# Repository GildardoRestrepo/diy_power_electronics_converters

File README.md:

# Portable Power Electronics Converters

Portable, enclosed power converters for teaching, sized to the supplies and loads of the Electric Machines Laboratory at Universidad Pontificia Bolivariana (UPB). Every unit follows the same path: calculation, simulation, PCB, build and lab validation. Each design can be reviewed and reproduced end to end.

> [!WARNING]
> These converters operate at up to 300 V DC and at mains-level AC. Build and test them only under lab supervision, with proper isolation and protection.

---

## Converters

| Family |             Converter             |     |
| :----: | :-------------------------------: | :-: |
| AC/DC  |  Three-phase full-wave rectifier  |     |
| DC/DC  |          Buck Converter           |     |
| DC/DC  |          Boost Converter          |     |
| DC/AC  | Three-phase full-wave (One level) |     |

### Rectifier
|              Parameter              |               Value               |                         Note                         |     |
| :---------------------------------: | :-------------------------------: | :--------------------------------------------------: | --- |
| Line voltage at the bridge (𝑉𝐿𝐿) |             208 Vrms              | Lab mains or transformer secondary of the same ratio |     |
|         Line frequency (𝑓)         |               60 Hz               |                       Colombia                       |     |
|       Rated DC current (𝐼𝑑)       |                5 A                |        Continuous, lamp bank or reactor load         |     |
|         Maximum DC current          |                8 A                |     10 min, heatsink-limited (see losses report)     |     |
|                Load                 | Resistive (lamps) or RL (reactor) |     𝐿𝑙𝑜𝑎𝑑 large enough for continuous 𝑖𝑑      |     |
|            Pulse number             |                 6                 |       Single box; 12 or 24 with several boxes        |     |

### Buck
|           Parameter            |                     Value                     |                    Note                    |
| :----------------------------: | :-------------------------------------------: | :----------------------------------------: |
|     Input voltage (𝑉𝑖𝑛)     |           280 V nominal, 150–320 V            | Rectifier output at 208 VLL; "300 V" class |
|     Output voltage (𝑉𝑜)      |                     110 V                     |              110 V lamp bank               |
|   Rated output power (𝑃𝑜)    |                     200 W                     |        Two 100 W lamps in parallel         |
|     Output current (𝐼𝑜)      |                    1.82 A                     |           𝑅 =𝑉2𝑜/𝑃𝑜 =60.5 Ω           |
|  Switching frequency (𝑓𝑠𝑤)  |        20 kHz nominal, 5–50 kHz usable        |   IGBT up to 20 kHz, MOSFET up to 50 kHz   |
| Inductor current ripple target |           ≤40 % of 𝐼𝑜 at nominal            |     Shared inductor with the boost box     |
|  Output voltage ripple target  |                     ≤1 %                      |                                            |
|            Control             | Open loop, duty cycle set on the gating block |        No feedback in this version         |

### Boost

|Parameter|Value|Note|
|:-:|:-:|:-:|
|Input voltage (𝑉𝑖𝑛)|110 V nominal, 60–120 V|Lab DC supply (110 V max.)|
|Output voltage (𝑉𝑜)|300 V|Feeds the buck or the inverter box, or a series lamp bank|
|Rated output power (𝑃𝑜)|200 W||
|Output current (𝐼𝑜)|0.667 A|𝑅 =𝑉2𝑜/𝑃𝑜 =450 Ω|
|Switching frequency (𝑓𝑠𝑤)|20 kHz nominal, 5–50 kHz usable|IGBT up to 20 kHz, MOSFET up to 50 kHz|
|Inductor current ripple target|≤40 % of 𝐼𝐿 at nominal|Same 4.7 mH inductor as the buck box|
|Output voltage ripple target|≤1 %||
|Control|Open loop, duty cycle set on the gating block|Over-voltage trip mandatory (see section 6)|

### Inverter

|          Parameter           |                             Value                              |                 Note                 |
| :--------------------------: | :------------------------------------------------------------: | :----------------------------------: |
|   DC-link voltage (𝑉𝑑𝑐)   |                    280 V nominal, 60–320 V                     |                                      |
|  Rated output power (𝑃𝑜)   |                             300 W                              |    Lamp bank (Y or Δ) or reactor     |
|     Rated phase current      |                             2 Arms                             |          𝐼𝑚 =2.83 A peak           |
|    Output frequency (𝑓1)    |                   0.1–400 Hz, 60 Hz default                    |                                      |
| Switching frequency (𝑓𝑠𝑤) |              10 kHz nominal (IGBT), up to 20 kHz               |                                      |
|          Modulation          | Sinusoidal PWM (𝑚𝑎 ≤1), six-step (180∘) and 120∘ square wave |     Selected on the gating block     |
|          Dead time           |                         1.5 𝜇s (IGBT)                         |    Generated by the gating block     |
|        Output filter         |              None on board (optional external LC)              | Lamps and reactor accept PWM voltage |

## Repository structure

The repository is organized by converter family. Every family uses the same five stages, and each stage is numbered after its family (e.g. `2x` for DC/DC).

```
├── 00_docs/
	├── datasheets/
	├── formulas/
	├── architecture.md
	├── gate_bus_interface.md
├── 01_rectifier/
	├── 00_assets/
	├── 10_math/
		├── 11_ideal.md
		├── 12_losses.md
	├── 20_psim/
		├── 20_ideal.psim
		├── 21_losses.psim
	├── 30_pcb/
		├── rectifier_6p/
		├── scripts/
			├── gen_rectifier.py
			├── pcb_config.JSON
	├── 40_building/
	├── 60_tests/
├── 02_buck/
	├── ...                      (same logic as 01)
├── 03_boost/
	├── ...                      (same logic as 01)
├── 04_inverter/
	├── ...                      (same logic as 01) 
├── 05_gating_block
	├── 10_math/
		├── signal_budget.md
	├── 30_pcb/
		├── gating_block/
		├── scripts/
			├── gen_gating_block.py
			├── pcb_config.JSON
├── 90_tools
├── LICENSE
└── README.md
```

---

## Workflow
1. **Math**: requirements, operating point and component sizing.
2. **Simulation**: validation in PSIM, first with ideal and then with real device models.
3. **Electronics design**: schematic and layout in KiCad.
4. **3d**: Case design in Fusion 360.
5. **Building**: Assembly and details.
6. **Tests:** lab tetsting and results.

---

## Tools & Software

|      Purpose      |                 Tool                  |
| :---------------: | :-----------------------------------: |
|    Simulation     |                 PSIM                  |
| Schematic and PCB |                 KiCad                 |
| Enclosure design  |              Fusion 360               |
| Switching control |          ESP32 + Arduino IDE          |
|     Lab tests     | Electrical Machines Laboratory at UPB |

---

## License

Released under the [MIT License](LICENSE).

---

## Enlaces

[[power_electronics|Power Electronics]]

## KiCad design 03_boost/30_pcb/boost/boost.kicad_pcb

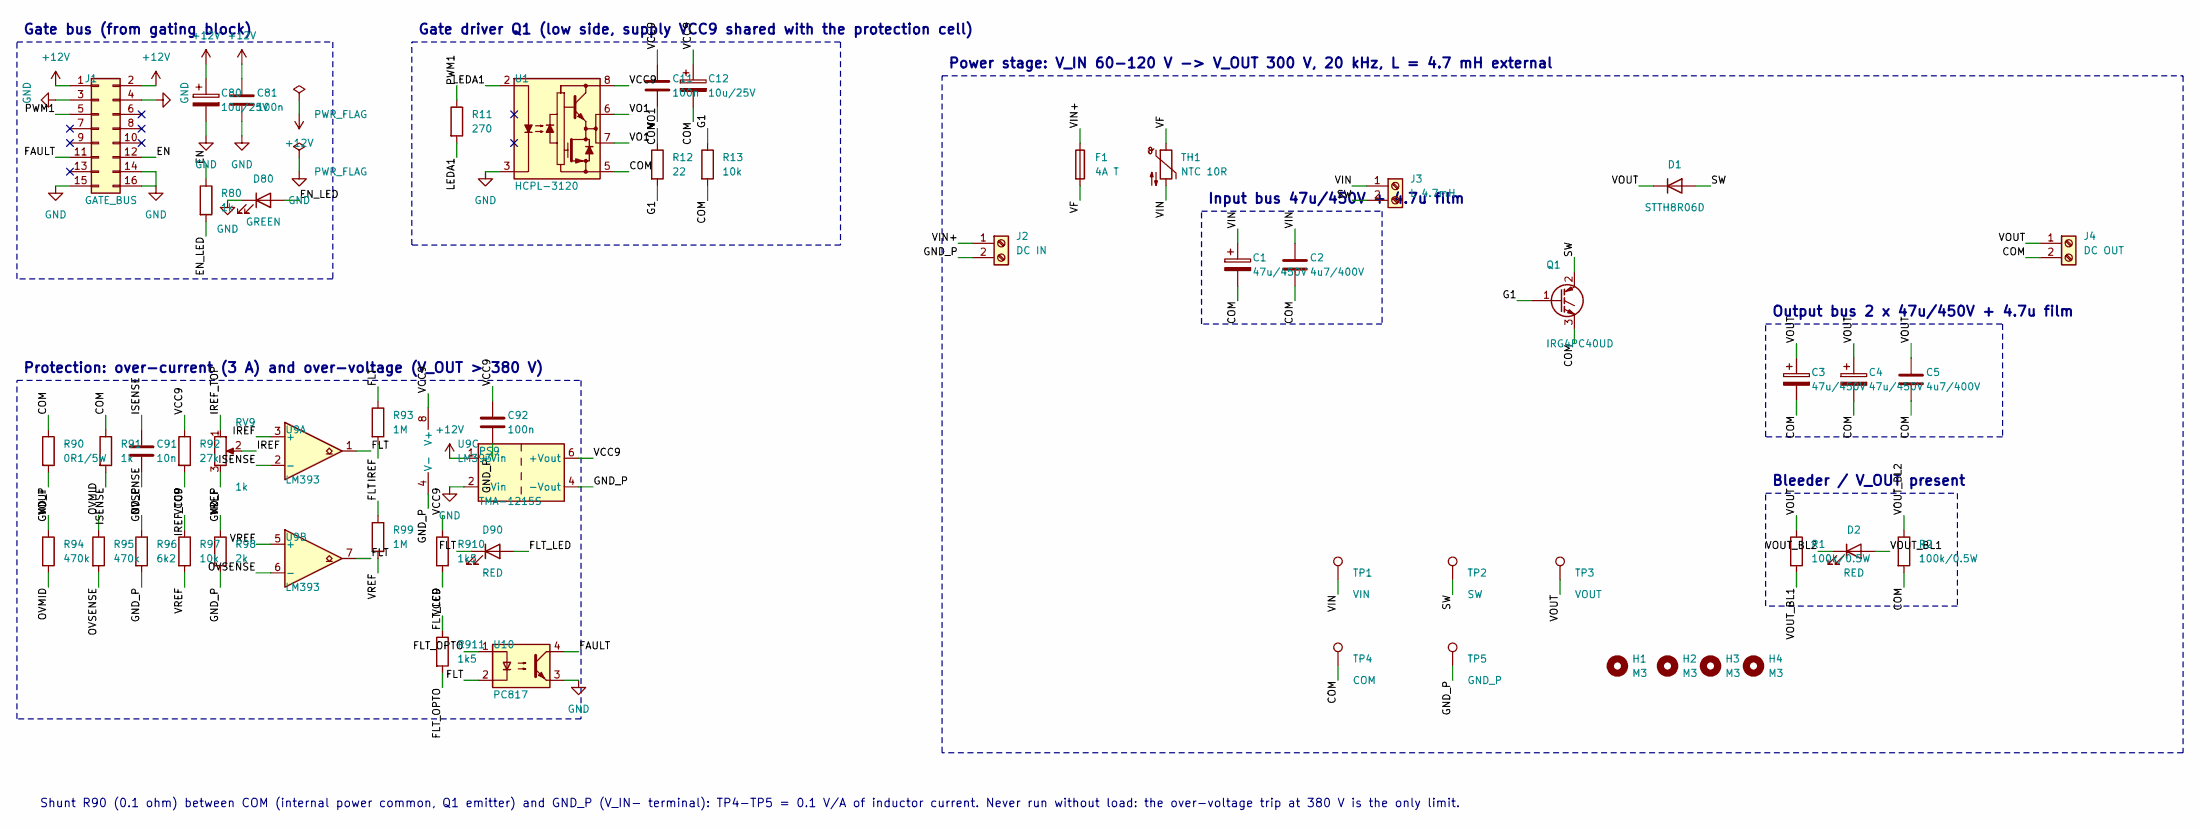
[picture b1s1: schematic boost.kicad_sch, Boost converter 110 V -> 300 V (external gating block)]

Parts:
C1, C3, C4: 47u/450V; C_Radial_D16.0mm_H25.0mm_P7.50mm
C2, C5: 4u7/400V; C_Rect_L31.5mm_W15.0mm_P27.50mm_MKS4
C11, C81, C92: 100n; C_Disc_D5.0mm_W2.5mm_P5.00mm
C12, C80: 10u/25V; C_Radial_D6.3mm_H11.0mm_P2.50mm
C91: 10n; C_Disc_D5.0mm_W2.5mm_P5.00mm
D1: STTH8R06D; TO-220-2_Vertical
D2: RED; LED_D5.0mm
D80: GREEN; LED_D3.0mm
D90: RED; LED_D3.0mm
F1: 4A T; Fuseholder_Cylinder-5x20mm_Schurter_0031_8201_Horizontal_Op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
H1, H2, H3, H4: M3; MountingHole_3.2mm_M3
J1: GATE_BUS; IDC-Header_2x08-1MP_P2.54mm_Latch9.5mm_Vertical
J2: DC IN; TerminalBlock_Phoenix_MKDS-1,5-2-5.08_1x02_P5.08mm_Horizont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
J3: L 4.7mH; TerminalBlock_Phoenix_MKDS-1,5-2-5.08_1x02_P5.08mm_Horizont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
J4: DC OUT; TerminalBlock_Phoenix_MKDS-1,5-2-5.08_1x02_P5.08mm_Horizont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
PS9: TMA-1215S; Converter_DCDC_TRACO_TMA-05xxS_12xxS_Single_THT
Q1: IRG4PC40UD; TO-247-3_Vertical
R1, R2: 100k/0.5W; R_Axial_DIN0414_L11.9mm_D4.5mm_P15.24mm_Horizontal
R11: 270; R_Axial_DIN0207_L6.3mm_D2.5mm_P10.16mm_Horizontal
R12: 22; R_Axial_DIN0207_L6.3mm_D2.5mm_P10.16mm_Horizontal
R13, R97: 10k; R_Axial_DIN0207_L6.3mm_D2.5mm_P10.16mm_Horizontal
R80, R91: 1k; R_Axial_DIN0207_L6.3mm_D2.5mm_P10.16mm_Horizontal
R90: 0R1/5W; R_Axial_Power_L20.0mm_W6.4mm_P25.40mm
R92: 27k; R_Axial_DIN0207_L6.3mm_D2.5mm_P10.16mm_Horizontal
R93, R99: 1M; R_Axial_DIN0207_L6.3mm_D2.5mm_P10.16mm_Horizontal
R94, R95: 470k; R_Axial_DIN0414_L11.9mm_D4.5mm_P15.24mm_Horizontal
R96: 6k2; R_Axial_DIN0207_L6.3mm_D2.5mm_P10.16mm_Horizontal
R98: 2k; R_Axial_DIN0207_L6.3mm_D2.5mm_P10.16mm_Horizontal
R910, R911: 1k5; R_Axial_DIN0207_L6.3mm_D2.5mm_P10.16mm_Horizontal
RV9: 1k; Potentiometer_Bourns_3296W_Vertical
TH1: NTC 10R; RV_Disc_D15.5mm_W4.2mm_P7.5mm
TP1: VIN; TestPoint_Loop_D2.50mm_Drill1.0mm
TP2: SW; TestPoint_Loop_D2.50mm_Drill1.0mm
TP3: VOUT; TestPoint_Loop_D2.50mm_Drill1.0mm
TP4: COM; TestPoint_Loop_D2.50mm_Drill1.0mm
TP5: GND_P; TestPoint_Loop_D2.50mm_Drill1.0mm
U1: HCPL-3120; DIP-8_W7.62mm
U9: LM393; DIP-8_W7.62mm
U10: PC817; DIP-4_W7.62mm

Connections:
+12V: C80.1, C81.1, J1.1, J1.2, PS9.1 (+Vin)
/COM: C1.2, C2.2, C3.2, C4.2, C5.2, C11.2, C12.2, J4.2, Q1.3 (E), R2.2, R13.2, R90.1, R91.1, TP4.1, U1.5 (VEE)
/EN: J1.12, R80.1
/EN_LED: D80.2 (A), R80.2
/FAULT: J1.11, U10.4
/FLT: D90.1 (K), R93.1, R99.1, U9.1, U9.7, U10.2
/FLT_LED: D90.2 (A), R910.2
/FLT_OPTO: R911.2, U10.1
/G1: Q1.1 (G), R12.2, R13.1
/GND_P: C91.2, C92.2, J2.2, PS9.4 (-Vout), R90.2, R96.2, R98.2, RV9.3, TP5.1, U9.4 (V-)
/IREF: R93.2, RV9.2, U9.3 (+)
/IREF_TOP: R92.2, RV9.1
/ISENSE: C91.1, R91.2, U9.2 (-)
/LEDA1: R11.2, U1.2 (A)
/OVMID: R94.2, R95.1
/OVSENSE: R95.2, R96.1, U9.6 (-)
/PWM1: J1.5, R11.1
/SW: D1.2 (A), J3.2, Q1.2 (C), TP2.1
/VCC9: C11.1, C12.1, C92.1, PS9.6 (+Vout), R92.1, R97.1, R910.1, R911.1, U1.8 (VCC), U9.8 (V+)
/VF: F1.2, TH1.1
/VIN: C1.1, C2.1, J3.1, TH1.2, TP1.1
/VIN+: F1.1, J2.1
/VO1: R12.1, U1.6 (VO), U1.7 (VO)
/VOUT: C3.1, C4.1, C5.1, D1.1 (K), J4.1, R1.1, R94.1, TP3.1
/VOUT_BL1: D2.2 (A), R1.2
/VOUT_BL2: D2.1 (K), R2.1
/VREF: R97.2, R98.1, R99.2, U9.5 (+)
GND: C80.2, C81.2, D80.1 (K), J1.3, J1.4, J1.14, J1.15, J1.16, PS9.2 (-Vin), U1.3 (C), U10.3

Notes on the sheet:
Gate bus (from gating block)
Gate driver Q1 (low side, supply VCC9 shared with the protection cell)
Protection: over-current (3 A) and over-voltage (V_OUT > 380 V)
Power stage: V_IN 60-120 V -> V_OUT 300 V, 20 kHz, L = 4.7 mH external
Input bus 47u/450V + 4.7u film
Output bus 2 x 47u/450V + 4.7u film
Bleeder / V_OUT present
Shunt R90 (0.1 ohm) between COM (internal power common, Q1 emitter) and GND_P (V_IN- terminal): TP4-TP5 = 0.1 V/A of inductor current. Never run without load: the over-voltage trip at 380 V is the only limit.

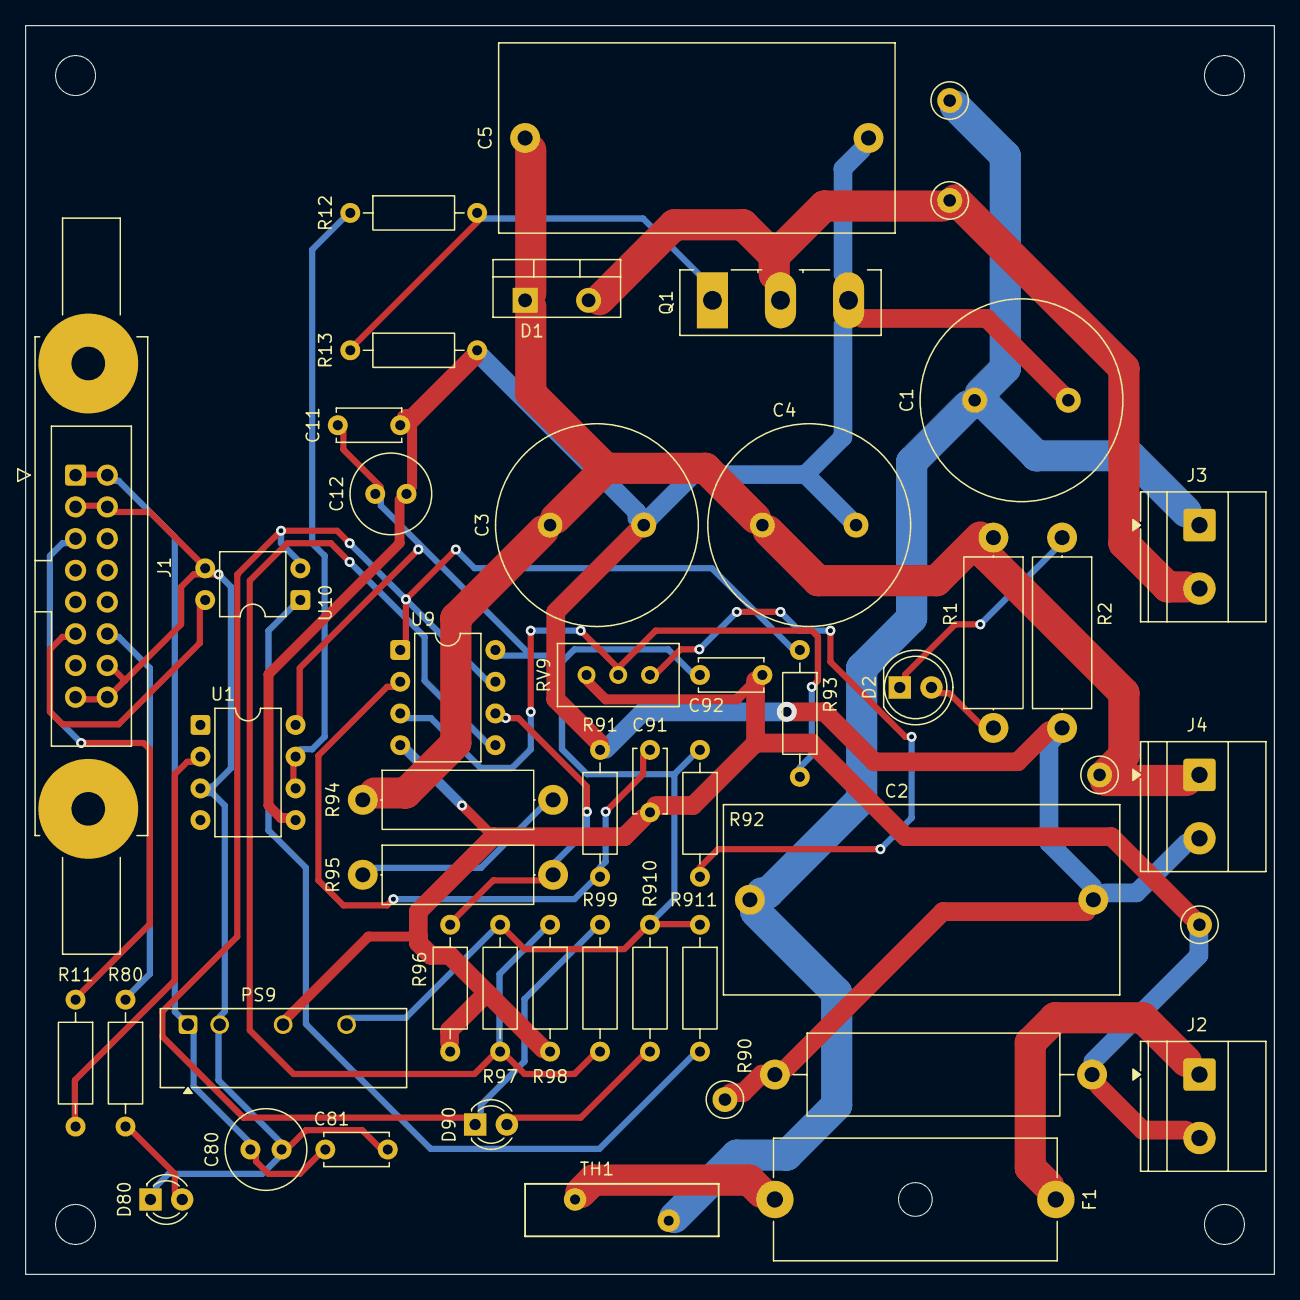
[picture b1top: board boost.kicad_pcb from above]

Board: 2 copper layers, 100.0 x 100.0 mm, 54 parts (0 on the bottom side), 28 nets.

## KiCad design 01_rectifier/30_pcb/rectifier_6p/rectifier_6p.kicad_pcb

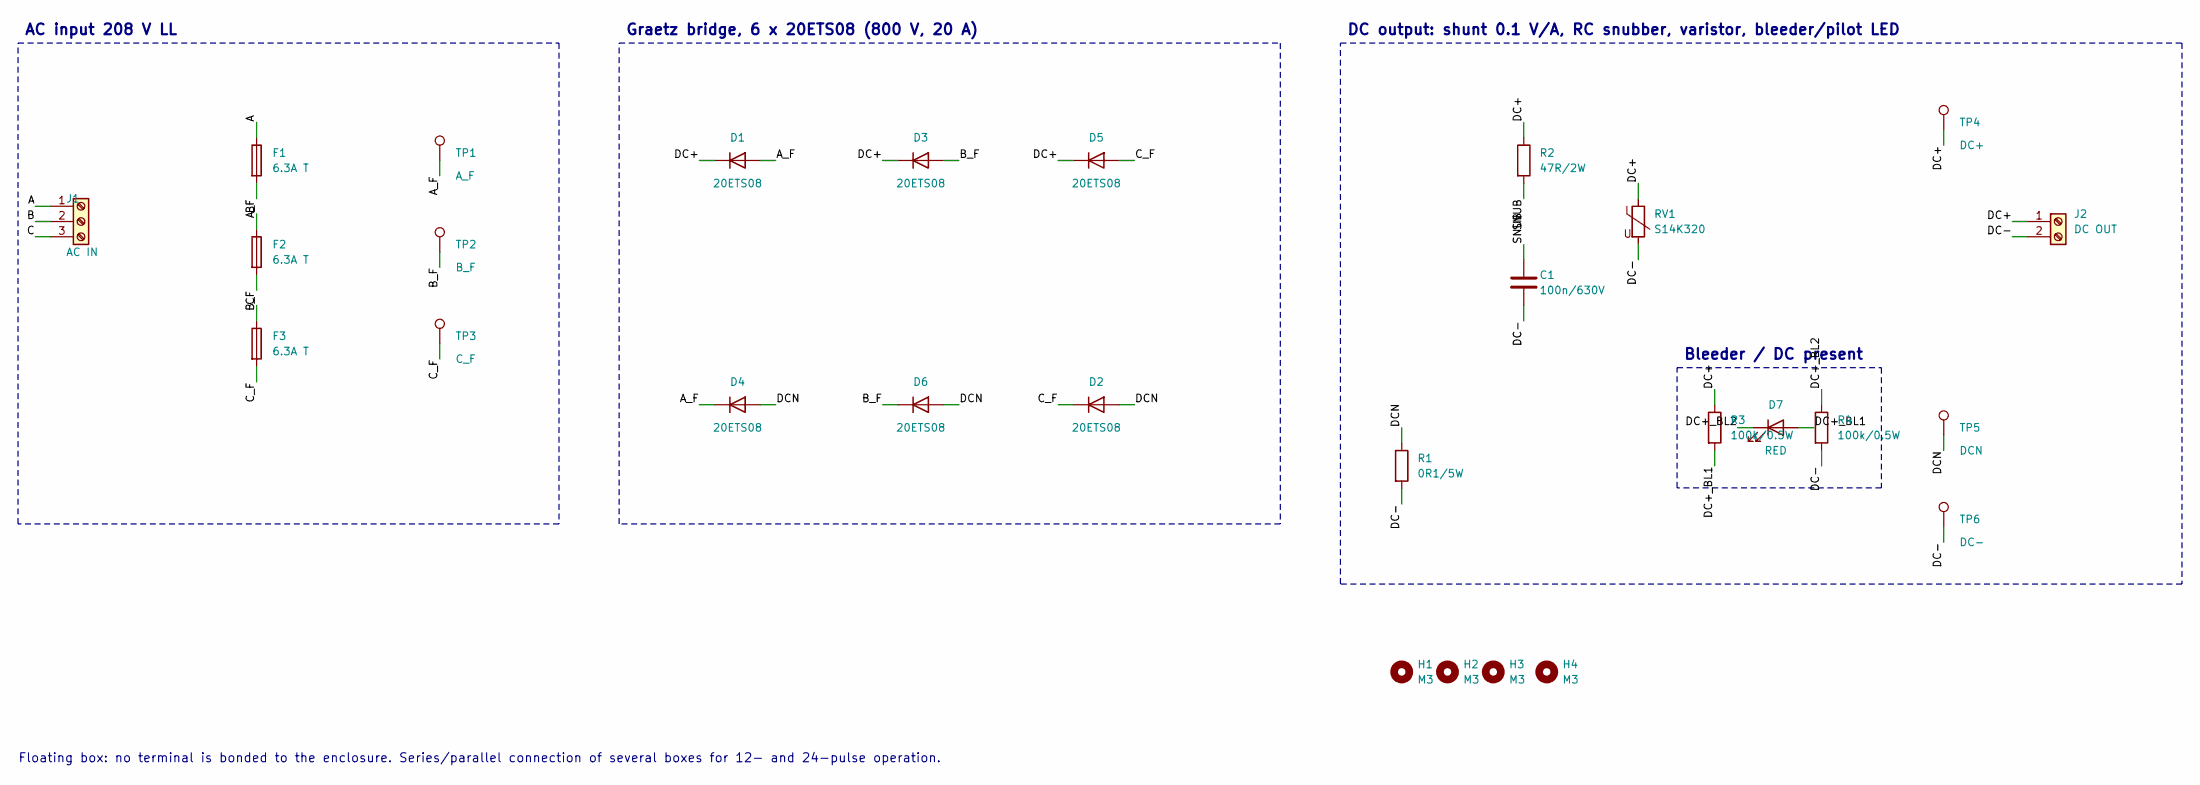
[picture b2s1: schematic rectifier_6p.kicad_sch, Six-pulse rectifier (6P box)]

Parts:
C1: 100n/630V; C_Rect_L13.0mm_W5.0mm_P10.00mm_FKS3_FKP3_MKS4
D1, D2, D3, D4, D5, D6: 20ETS08; TO-220-2_Vertical
D7: RED; LED_D5.0mm
F1, F2, F3: 6.3A T; Fuseholder_Cylinder-5x20mm_Schurter_0031_8201_Horizontal_Op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
H1, H2, H3, H4: M3; MountingHole_3.2mm_M3
J1: AC IN; TerminalBlock_Phoenix_MKDS-1,5-3-5.08_1x03_P5.08mm_Horizont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
J2: DC OUT; TerminalBlock_Phoenix_MKDS-1,5-2-5.08_1x02_P5.08mm_Horizont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
R1: 0R1/5W; R_Axial_Power_L20.0mm_W6.4mm_P25.40mm
R2: 47R/2W; R_Axial_DIN0617_L17.0mm_D6.0mm_P20.32mm_Horizontal
R3, R4: 100k/0.5W; R_Axial_DIN0414_L11.9mm_D4.5mm_P15.24mm_Horizontal
RV1: S14K320; RV_Disc_D15.5mm_W4.2mm_P7.5mm
TP1: A_F; TestPoint_Loop_D2.50mm_Drill1.0mm
TP2: B_F; TestPoint_Loop_D2.50mm_Drill1.0mm
TP3: C_F; TestPoint_Loop_D2.50mm_Drill1.0mm
TP4: DC+; TestPoint_Loop_D2.50mm_Drill1.0mm
TP5: DCN; TestPoint_Loop_D2.50mm_Drill1.0mm
TP6: DC-; TestPoint_Loop_D2.50mm_Drill1.0mm

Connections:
/A: F1.1, J1.1
/A_F: D1.2 (A), D4.1 (K), F1.2, TP1.1
/B: F2.1, J1.2
/B_F: D3.2 (A), D6.1 (K), F2.2, TP2.1
/C: F3.1, J1.3
/C_F: D2.1 (K), D5.2 (A), F3.2, TP3.1
/DC+: D1.1 (K), D3.1 (K), D5.1 (K), J2.1, R2.1, R3.1, RV1.1, TP4.1
/DC+_BL1: D7.2 (A), R3.2
/DC+_BL2: D7.1 (K), R4.1
/DC-: C1.2, J2.2, R1.2, R4.2, RV1.2, TP6.1
/DCN: D2.2 (A), D4.2 (A), D6.2 (A), R1.1, TP5.1
/SNUB: C1.1, R2.2

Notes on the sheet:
AC input 208 V LL
Graetz bridge, 6 x 20ETS08 (800 V, 20 A)
DC output: shunt 0.1 V/A, RC snubber, varistor, bleeder/pilot LED
Bleeder / DC present
Floating box: no terminal is bonded to the enclosure. Series/parallel connection of several boxes for 12- and 24-pulse operation.

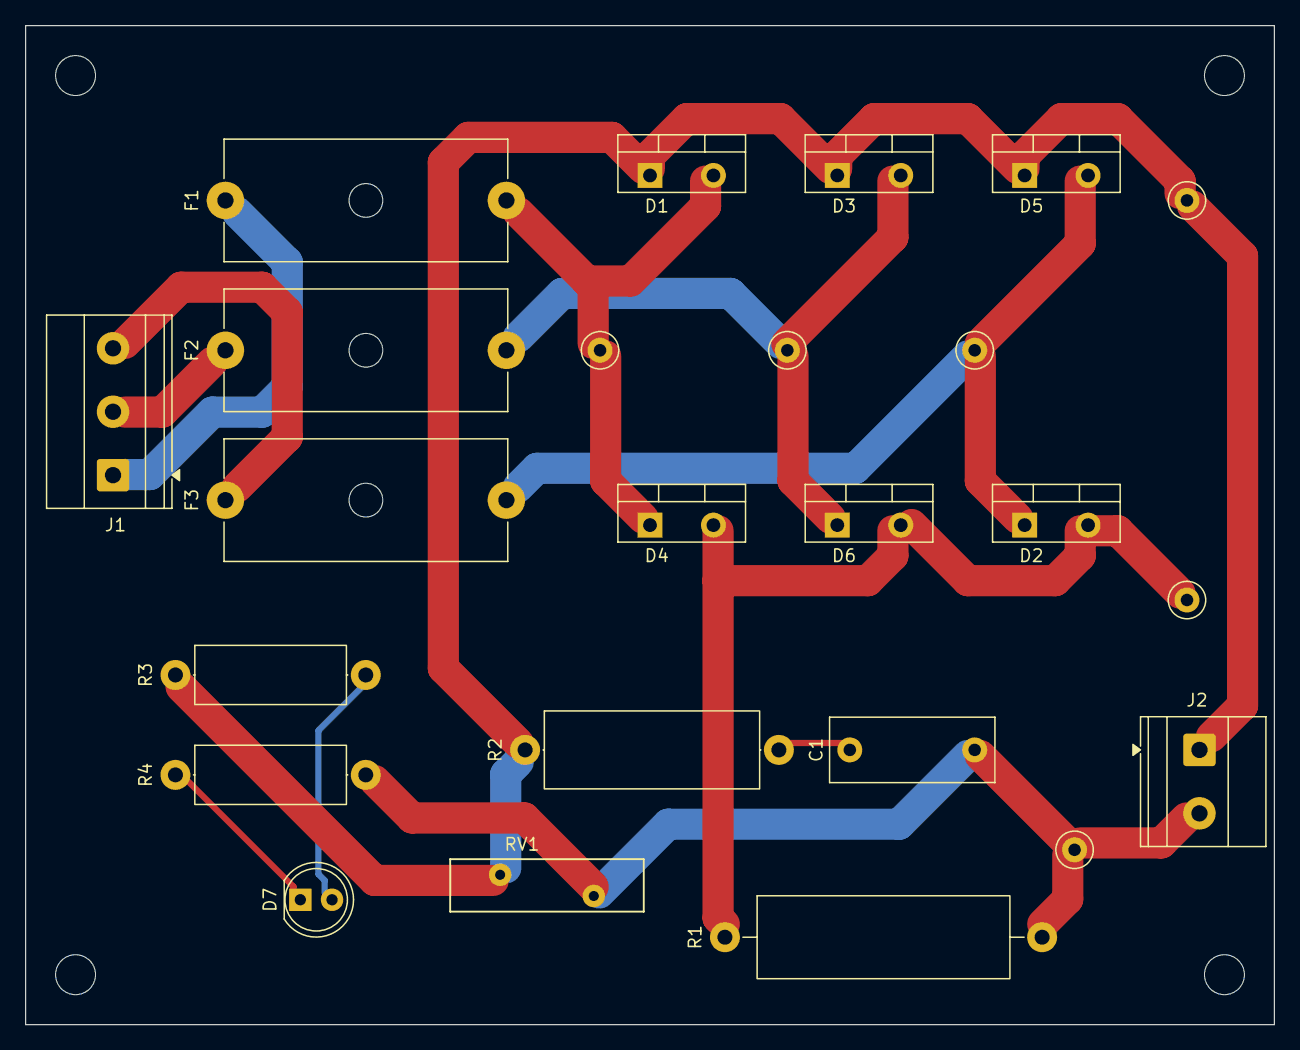
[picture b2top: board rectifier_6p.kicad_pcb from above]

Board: 2 copper layers, 100.0 x 80.0 mm, 28 parts (0 on the bottom side), 12 nets.

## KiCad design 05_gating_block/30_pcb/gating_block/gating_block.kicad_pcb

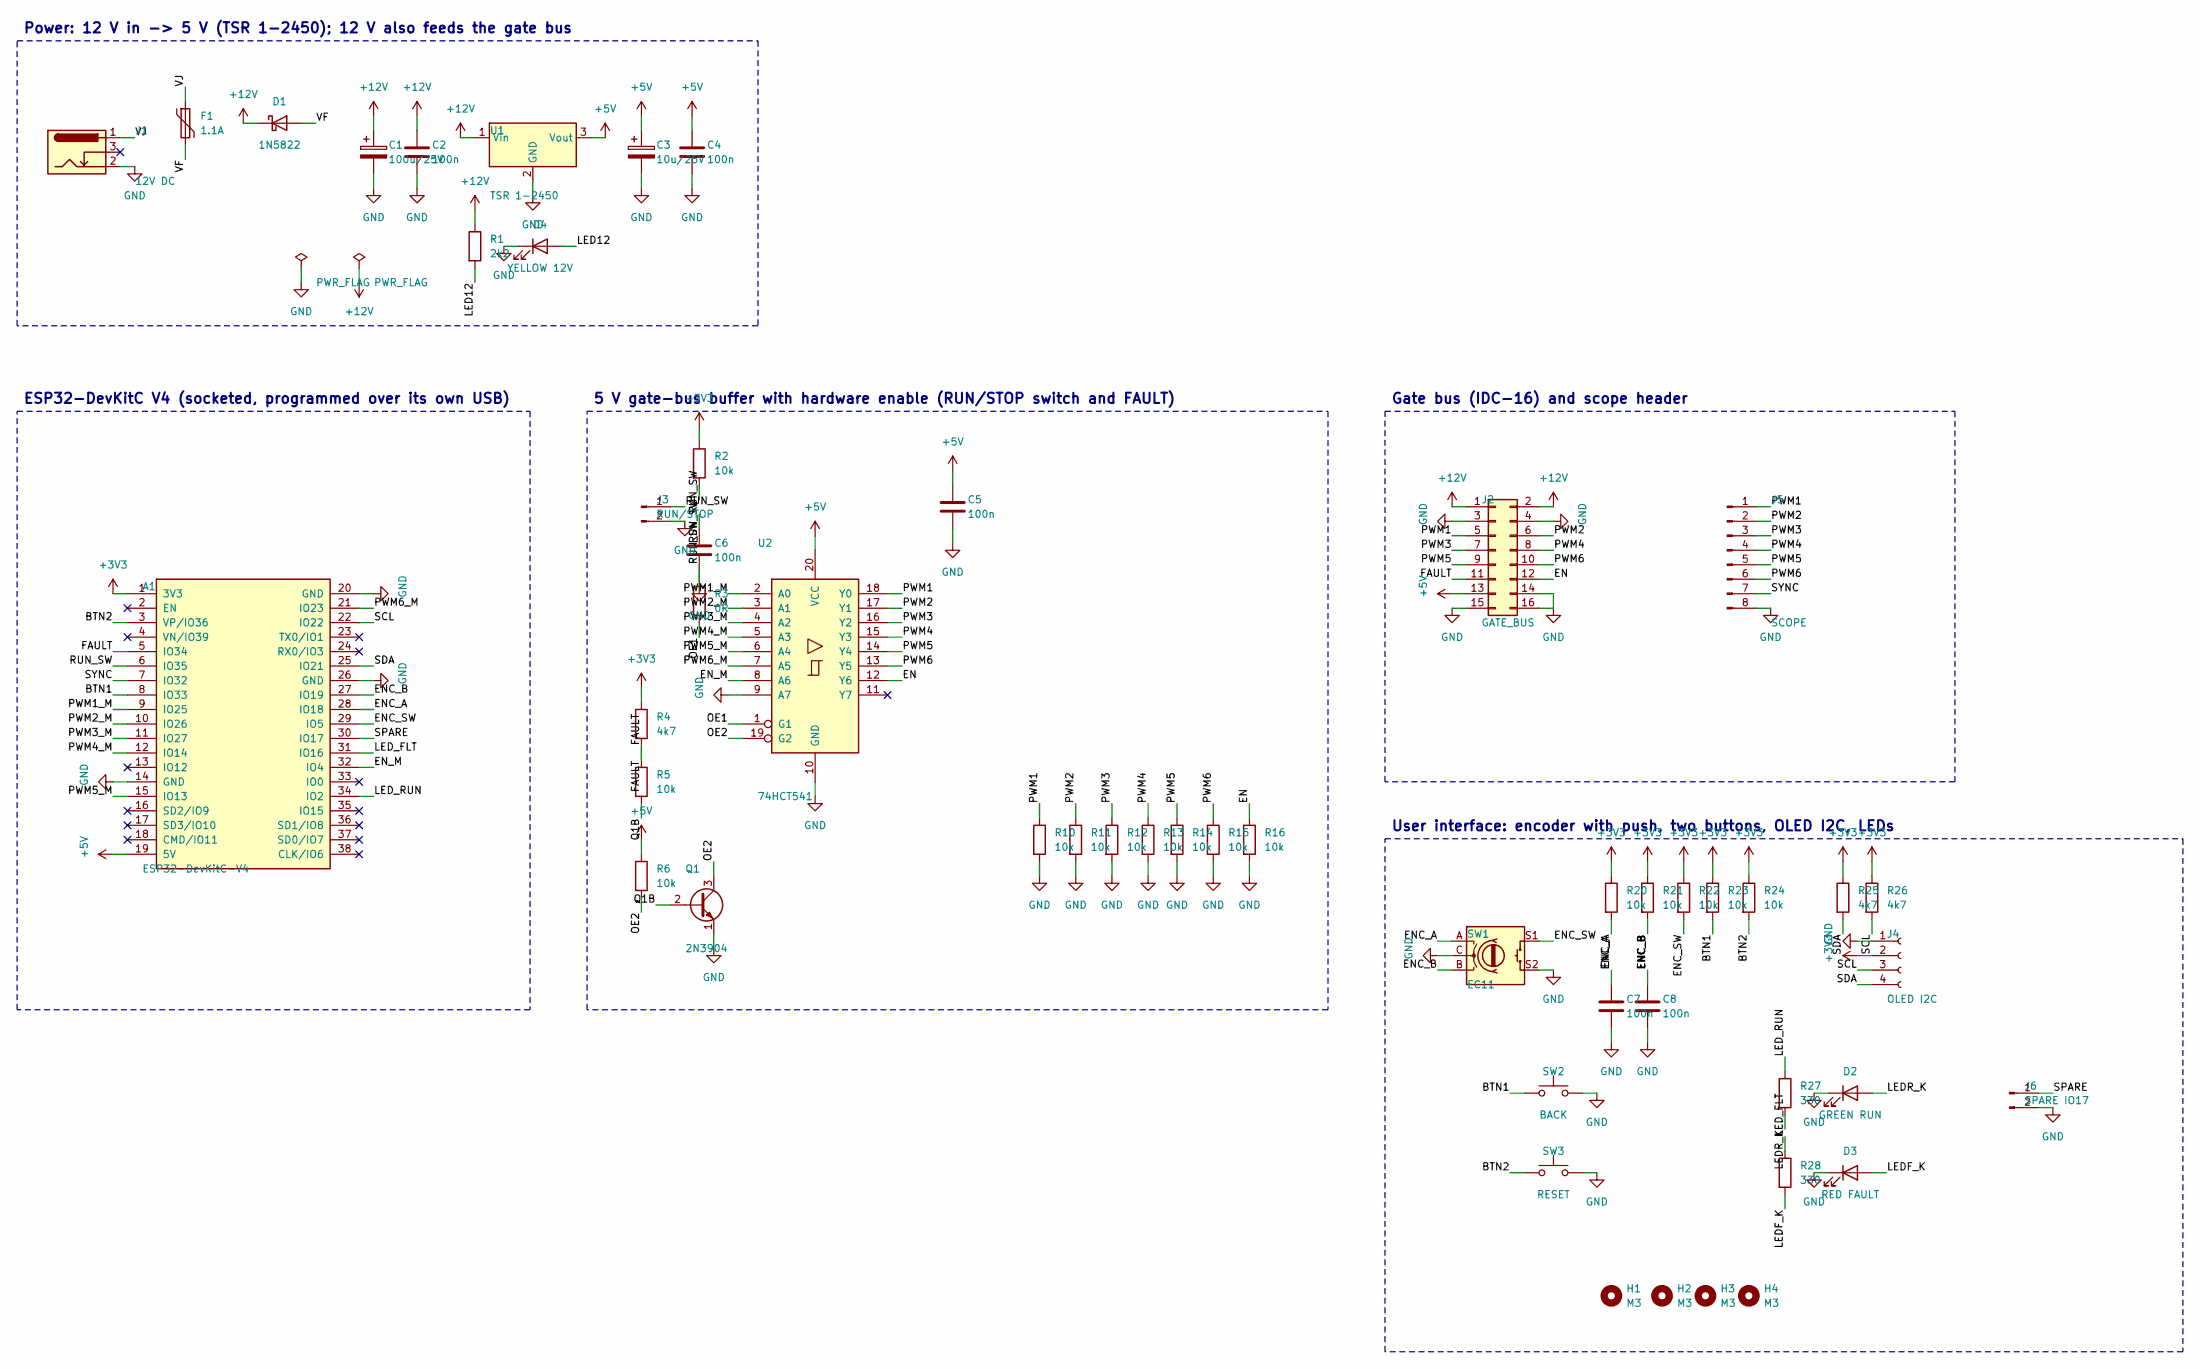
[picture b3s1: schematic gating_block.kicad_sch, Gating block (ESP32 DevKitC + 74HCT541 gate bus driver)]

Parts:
A1: ESP32-DevKitC-V4; ESP32-DevKitC-V4_Socket
C1: 100u/25V; C_Radial_D8.0mm_H11.5mm_P3.50mm
C2, C4, C5, C6, C7, C8: 100n; C_Disc_D5.0mm_W2.5mm_P5.00mm
C3: 10u/25V; C_Radial_D5.0mm_H11.0mm_P2.00mm
D1: 1N5822; D_DO-201AD_P15.24mm_Horizontal
D2: GREEN RUN; LED_D3.0mm
D3: RED FAULT; LED_D3.0mm
D4: YELLOW 12V; LED_D3.0mm
F1: 1.1A; Fuse_Bourns_MF-RG1100
H1, H2, H3, H4: M3; MountingHole_3.2mm_M3
J1: 12V DC; BarrelJack_Horizontal
J2: GATE_BUS; IDC-Header_2x08-1MP_P2.54mm_Latch9.5mm_Vertical
J3: RUN/STOP; PinHeader_1x02_P2.54mm_Vertical
J4: OLED I2C; PinSocket_1x04_P2.54mm_Vertical
J5: SCOPE; PinHeader_1x08_P2.54mm_Vertical
J6: SPARE IO17; PinHeader_1x02_P2.54mm_Vertical
Q1: 2N3904; TO-92_Inline
R1: 2k2; R_Axial_DIN0207_L6.3mm_D2.5mm_P10.16mm_Horizontal
R2, R5, R6, R10, R11, R12, R13, R14, R15, R16, R20, R21, R22, R23, R24: 10k; R_Axial_DIN0207_L6.3mm_D2.5mm_P10.16mm_Horizontal
R3: 0R; R_Axial_DIN0207_L6.3mm_D2.5mm_P10.16mm_Horizontal
R4, R25, R26: 4k7; R_Axial_DIN0207_L6.3mm_D2.5mm_P10.16mm_Horizontal
R27, R28: 330; R_Axial_DIN0207_L6.3mm_D2.5mm_P10.16mm_Horizontal
SW1: EC11; RotaryEncoder_Alps_EC11E-Switch_Vertical_H20mm
SW2: BACK; SW_PUSH_6mm_H13mm
SW3: RESET; SW_PUSH_6mm_H13mm
U1: TSR 1-2450; Converter_DCDC_TRACO_TSR-1_THT
U2: 74HCT541; DIP-20_W7.62mm

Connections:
+3V3: A1.1 (3V3), J4.2, R2.1, R4.1, R20.1, R21.1, R22.1, R23.1, R24.1, R25.1, R26.1
+5V: A1.19 (5V), C3.1, C4.1, C5.1, J2.13, R6.1, U1.3 (Vout), U2.20 (VCC)
+12V: C1.1, C2.1, D1.1 (K), J2.1, J2.2, R1.1, U1.1 (Vin)
/BTN1: A1.8 (IO33), R23.2, SW2.1
/BTN2: A1.3 (VP/IO36), R24.2, SW3.1
/EN: J2.12, R16.1, U2.12 (Y6)
/ENC_A: A1.28 (IO18), C7.1, R20.2, SW1.A
/ENC_B: A1.27 (IO19), C8.1, R21.2, SW1.B
/ENC_SW: A1.29 (IO5), R22.2, SW1.S1
/EN_M: A1.32 (IO4), U2.8 (A6)
/FAULT: A1.5 (IO34), J2.11, R4.2, R5.1
/LED12: D4.2 (A), R1.2
/LEDF_K: D3.2 (A), R28.2
/LEDR_K: D2.2 (A), R27.2
/LED_FLT: A1.31 (IO16), R28.1
/LED_RUN: A1.34 (IO2), R27.1
/OE1: R3.2, U2.1 (G1)
/OE2: Q1.3 (C), R6.2, U2.19 (G2)
/PWM1: J2.5, J5.1, R10.1, U2.18 (Y0)
/PWM1_M: A1.9 (IO25), U2.2 (A0)
/PWM2: J2.6, J5.2, R11.1, U2.17 (Y1)
/PWM2_M: A1.10 (IO26), U2.3 (A1)
/PWM3: J2.7, J5.3, R12.1, U2.16 (Y2)
/PWM3_M: A1.11 (IO27), U2.4 (A2)
/PWM4: J2.8, J5.4, R13.1, U2.15 (Y3)
/PWM4_M: A1.12 (IO14), U2.5 (A3)
/PWM5: J2.9, J5.5, R14.1, U2.14 (Y4)
/PWM5_M: A1.15 (IO13), U2.6 (A4)
/PWM6: J2.10, J5.6, R15.1, U2.13 (Y5)
/PWM6_M: A1.21 (IO23), U2.7 (A5)
/Q1B: Q1.2 (B), R5.2
/RUN_SW: A1.6 (IO35), C6.1, J3.1, R2.2, R3.1
/SCL: A1.22 (IO22), J4.3, R26.2
/SDA: A1.25 (IO21), J4.4, R25.2
/SPARE: A1.30 (IO17), J6.1
/SYNC: A1.7 (IO32), J5.7
/VF: D1.2 (A), F1.2
/VJ: F1.1, J1.1
GND: A1.14 (GND), A1.20 (GND), A1.26 (GND), C1.2, C2.2, C3.2, C4.2, C5.2, C6.2, C7.2, C8.2, D2.1 (K), D3.1 (K), D4.1 (K), J1.2, J2.3, J2.4, J2.14, J2.15, J2.16, J3.2, J4.1, J5.8, J6.2, Q1.1 (E), R10.2, R11.2, R12.2, R13.2, R14.2, R15.2, R16.2, SW1.C, SW1.S2, SW2.2, SW3.2, U1.2 (GND), U2.9 (A7), U2.10 (GND)

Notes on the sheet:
Power: 12 V in -> 5 V (TSR 1-2450); 12 V also feeds the gate bus
ESP32-DevKitC V4 (socketed, programmed over its own USB)
5 V gate-bus buffer with hardware enable (RUN/STOP switch and FAULT)
Gate bus (IDC-16) and scope header
User interface: encoder with push, two buttons, OLED I2C, LEDs

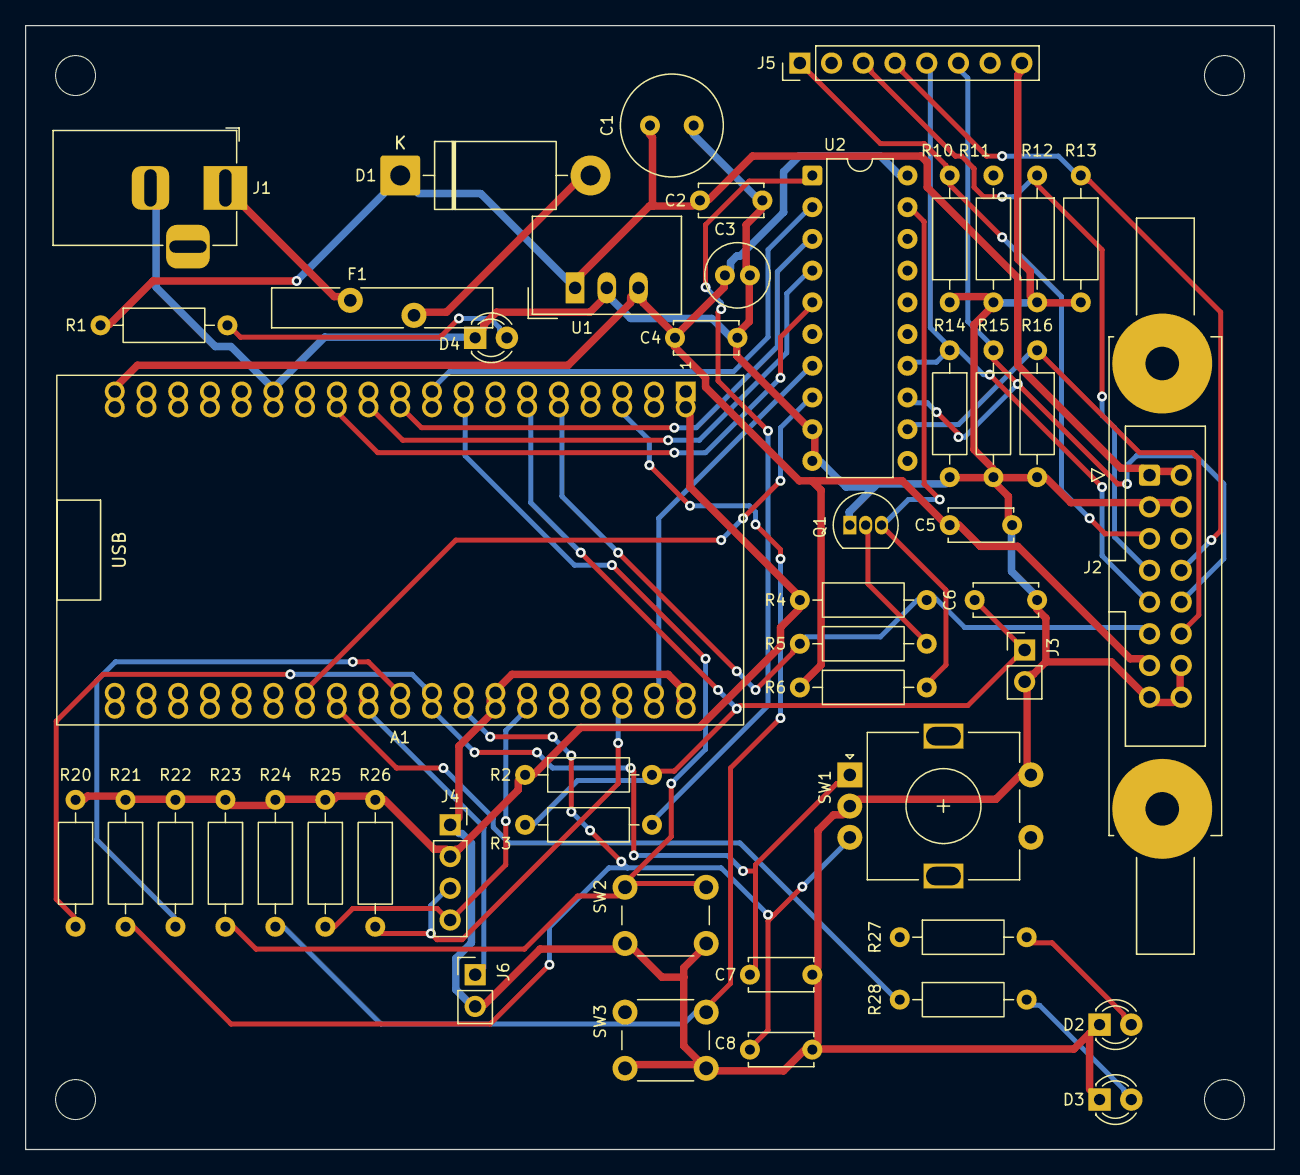
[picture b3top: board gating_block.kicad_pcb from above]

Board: 2 copper layers, 100.0 x 90.0 mm, 52 parts (0 on the bottom side), 39 nets.
